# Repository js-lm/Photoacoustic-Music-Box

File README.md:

# Photoacoustic Music Box

A WIP project, the goal is to use light to make music via the photoacoustic effect.

## About The Project

Most studies and research on photoacoustics have used lasers, and some have even used sunlight.

For my use case, lasers are not a good fit since they are either too weak to produce any noticeable sound or too strong and will melt the material. I also don't have those thousand-dollar lasers designed specifically for the lab.

Using the sun is an interesting idea, but there are a few issues. First, I want more than just to generate audio; I want to make music! This means the frequency needed is much higher than what a spin wheel can achieve. Not to mention, you will need to be able to accelerate and decelerate the wheel very quickly, which is just not possible. Second, ~~I hate the sun~~, using the sun means that I need to do a lot of the testing outside, which is just not that convenient.

So I decided to try using a high-wattage LED, and I can even reuse my old projector LED. Although later I decided to buy a new LED.

I actually just found out that there are people who managed to use an ordinary LED and BUTTERFLY WINGS (!!!) to generate over 70dB music. They even published a paper! Just today (2026-10-26)! ([When Butterfly Meets Photoacoustic Effect](https://dl.acm.org/doi/10.1145/3795866.3844464))

It's actually good news for me. Now I know for sure this is actually feasible. Of course, I am not going to use butterfly wings, but probably just soot on mesh, which is what most other people use. So there is still a chance that it won't work as well.

Anyway, to drive the LED, I designed a custom PCB to generate the high-speed pulsing needed. 

My original design was pretty simple and straightforward: A Pi Pico generates the pulse signal, and a gate driver switches a power MOSFET that drives the CXB3590 LED from a 48V input. The LED current is set by 4 paralleled 0.39 Ω sense resistors, and an on-board 12V rail feeds a 5V regulator for the logic.

But since I am pretty new to designing circuits, especially high-power one, I was like, "let's see what the AI has to say about it." Claude absolutely roasted my design and told me 3 million different ways that it could kill me. Ok, whatever, I listened to its advice, modified the design a bit, and added a buttload of safety features. Which, to be fair, is a good idea anyway.

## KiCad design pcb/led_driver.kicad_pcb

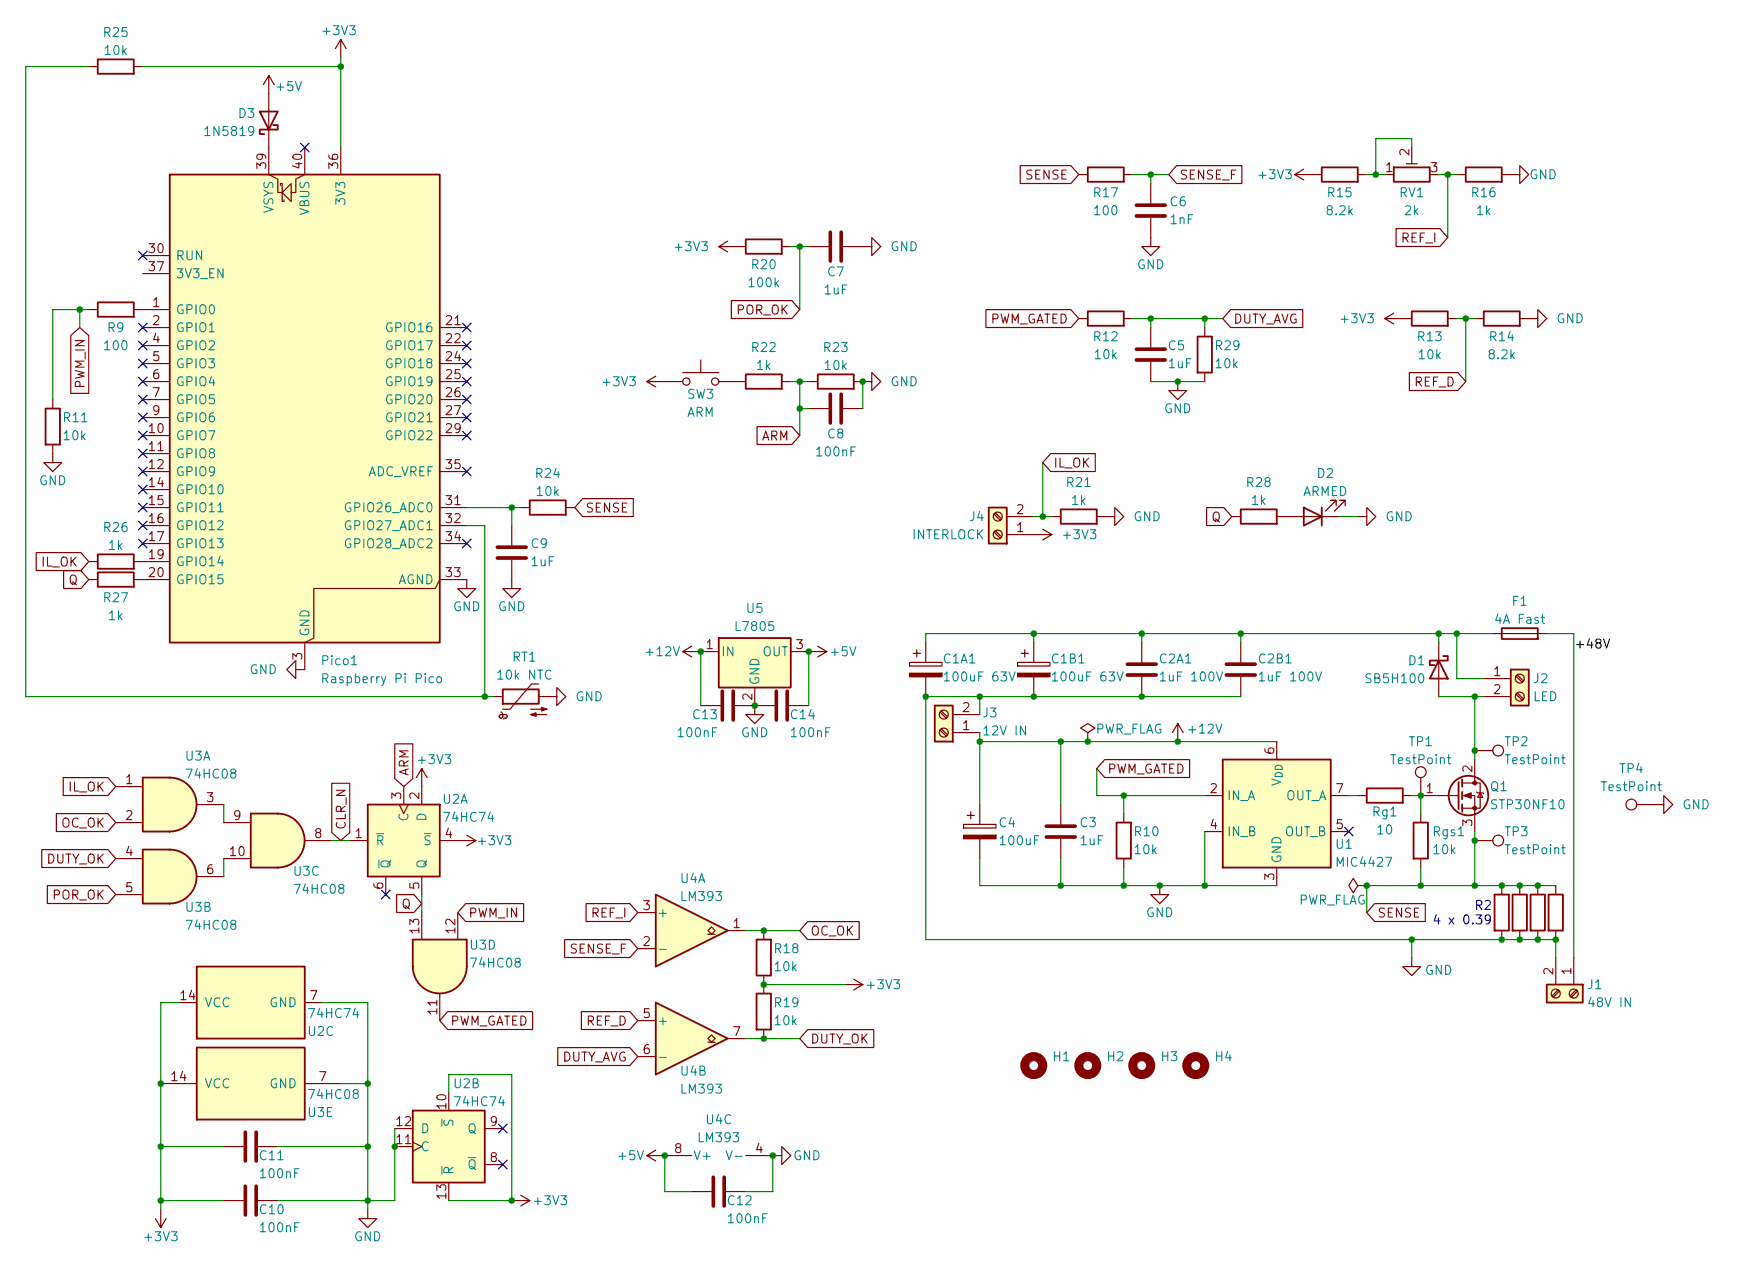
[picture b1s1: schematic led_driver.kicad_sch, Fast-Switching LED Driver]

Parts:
C1A1, C1B1: 100uF 63V; CP_Radial_D10.0mm_P5.00mm
C2A1, C2B1: 1uF 100V; C_Rect_L7.2mm_W4.5mm_P5.00mm_FKS2_FKP2_MKS2_MKP2
C3, C5, C7, C9: 1uF; C_Rect_L7.2mm_W4.5mm_P5.00mm_FKS2_FKP2_MKS2_MKP2
C4: 100uF; CP_Radial_D6.3mm_P2.50mm
C6: 1nF; C_Rect_L7.2mm_W4.5mm_P5.00mm_FKS2_FKP2_MKS2_MKP2
C8, C10, C11, C12, C13, C14: 100nF; C_Rect_L7.2mm_W4.5mm_P5.00mm_FKS2_FKP2_MKS2_MKP2
D1: SB5H100; D_DO-201AD_P5.08mm_Vertical_CathodeUp
D2: ARMED; LED_D5.0mm
D3: 1N5819; D_DO-41_SOD81_P10.16mm_Horizontal
F1: 4A Fast; Fuseholder_Cylinder-5x20mm_Schurter_0031_8201_Horizontal_Op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
H1, H2, H3, H4: MountingHole; MountingHole_2.2mm_M2
J1: 48V IN; TerminalBlock_Phoenix_MKDS-1,5-2-5.08_1x02_P5.08mm_Horizont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
J2: LED; TerminalBlock_Phoenix_MKDS-1,5-2-5.08_1x02_P5.08mm_Horizont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
J3: 12V IN; TerminalBlock_Phoenix_MKDS-1,5-2-5.08_1x02_P5.08mm_Horizont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
J4: INTERLOCK; TerminalBlock_Phoenix_MKDS-1,5-2-5.08_1x02_P5.08mm_Horizont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
Pico1: Raspberry Pi Pico; RaspberryPi_Pico_Common_THT
Q1: STP30NF10; TO-220-3_Vertical
R2A1, R2B1, R2C1, R2D1: 0.39; R_Axial_DIN0207_L6.3mm_D2.5mm_P2.54mm_Vertical
R9, R17: 100; R_Axial_DIN0207_L6.3mm_D2.5mm_P10.16mm_Horizontal
R10, R11, R12, R13, R18, R19, R23, R24, R25, R29: 10k; R_Axial_DIN0207_L6.3mm_D2.5mm_P10.16mm_Horizontal
R14, R15: 8.2k; R_Axial_DIN0207_L6.3mm_D2.5mm_P10.16mm_Horizontal
R16, R21, R22, R26, R27, R28: 1k; R_Axial_DIN0207_L6.3mm_D2.5mm_P10.16mm_Horizontal
R20: 100k; R_Axial_DIN0207_L6.3mm_D2.5mm_P10.16mm_Horizontal
RT1: 10k NTC; PinHeader_1x02_P2.54mm_Vertical
RV1: 2k; Potentiometer_Bourns_3296W_Vertical
Rg1: 10; R_Axial_DIN0207_L6.3mm_D2.5mm_P2.54mm_Vertical
Rgs1: 10k; R_Axial_DIN0207_L6.3mm_D2.5mm_P2.54mm_Vertical
SW3: ARM; SW_PUSH_6mm
TP1, TP2, TP3, TP4: TestPoint; TestPoint_THTPad_D2.0mm_Drill1.0mm
U1: MIC4427; SOIC-8_3.9x4.9mm_P1.27mm
U2: 74HC74; DIP-14_W7.62mm
U3: 74HC08; DIP-14_W7.62mm
U4: LM393; DIP-8_W7.62mm
U5: L7805; TO-220-3_Vertical

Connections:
+3V3: C10.1, C11.1, J4.1, Pico1.36 (3V3), R13.1, R15.1, R18.1, R19.1, R20.1, R25.2, SW3.1, U2.2 (D), U2.4 (~S), U2.10 (~S), U2.13 (~R), U2.14 (VCC), U3.14 (VCC)
+5V: C12.1, C14.2, D3.2 (A), U4.8 (V+), U5.3 (OUT)
+12V: C3.1, C4.1, C13.1, J3.1, U1.6 (V_{DD}), U5.1 (IN)
/+48V: F1.2, J1.1
ARM: C8.1, R22.2, R23.1, U2.3 (C)
CLR_N: U2.1 (~R), U3.8
DUTY_AVG: C5.1, R12.2, R29.1, U4.6 (-)
DUTY_OK: R19.2, U3.4, U4.7
GND: C1A1.2, C1B1.2, C2A1.2, C2B1.2, C3.2, C4.2, C5.2, C6.2, C7.2, C8.2, C9.2, C10.2, C11.2, C12.2, C13.2, C14.1, D2.1 (K), J1.2, J3.2, Pico1.3 (GND), Pico1.8 (GND), Pico1.13 (GND), Pico1.18 (GND), Pico1.23 (GND), Pico1.28 (GND), Pico1.33 (AGND), Pico1.38 (GND), R2A1.2, R2B1.2, R2C1.2, R2D1.2, R10.1, R11.2, R14.2, R16.2, R21.2, R23.2, R29.2, RT1.2, TP4.1 (1_1), U1.3 (GND), U1.4 (IN_B), U2.7 (GND), U2.11 (C), U2.12 (D), U3.7 (GND), U4.4 (V-), U5.2 (GND)
IL_OK: J4.2, R21.1, R26.1, U3.1
unnamed: D1.2 (A), J2.2, Q1.2 (D), TP2.1 (1_1)
unnamed: C1A1.1, C1B1.1, C2A1.1, C2B1.1, D1.1 (K), F1.1, J2.1
unnamed: D2.2 (A), R28.2
unnamed: D3.1 (K), Pico1.39 (VSYS)
unnamed: Pico1.1 (GPIO0), R9.2
unnamed: Pico1.19 (GPIO14), R26.2
unnamed: Pico1.20 (GPIO15), R27.2
unnamed: C9.1, Pico1.31 (GPIO26_ADC0), R24.1
unnamed: Pico1.32 (GPIO27_ADC1), R25.1, RT1.1
unnamed: Q1.1 (G), Rg1.2, Rgs1.1, TP1.1 (1_1)
unnamed: R15.2, RV1.1, RV1.2
unnamed: R22.1, SW3.2
unnamed: Rg1.1, U1.7 (OUT_A)
unnamed: U3.3, U3.9
unnamed: U3.6, U3.10
OC_OK: R18.2, U3.2, U4.1
POR_OK: C7.1, R20.2, U3.5
PWM_GATED: R10.2, R12.1, U1.2 (IN_A), U3.11
PWM_IN: R9.1, R11.1, U3.12
Q: R27.1, R28.1, U2.5 (Q), U3.13
REF_D: R13.2, R14.1, U4.5 (+)
REF_I: R16.1, RV1.3, U4.3 (+)
SENSE: Q1.3 (S), R2A1.1, R2B1.1, R2C1.1, R2D1.1, R17.1, R24.2, Rgs1.2, TP3.1 (1_1)
SENSE_F: C6.1, R17.2, U4.2 (-)

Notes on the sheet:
R2 4 x 0.39

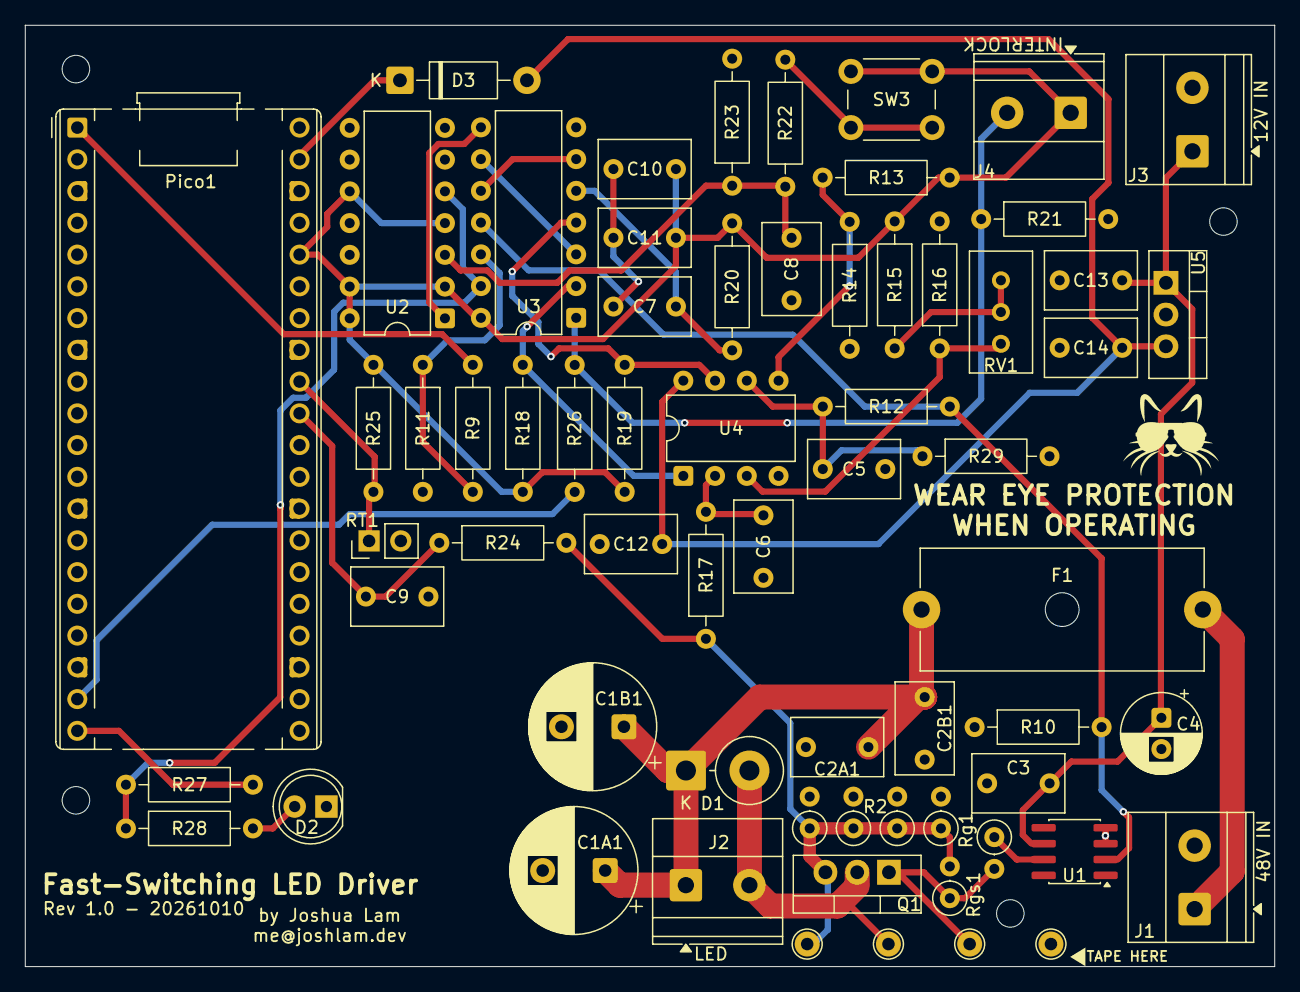
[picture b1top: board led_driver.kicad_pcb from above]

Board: 2 copper layers, 100.0 x 75.3 mm, 69 parts (0 on the bottom side), 34 nets.
